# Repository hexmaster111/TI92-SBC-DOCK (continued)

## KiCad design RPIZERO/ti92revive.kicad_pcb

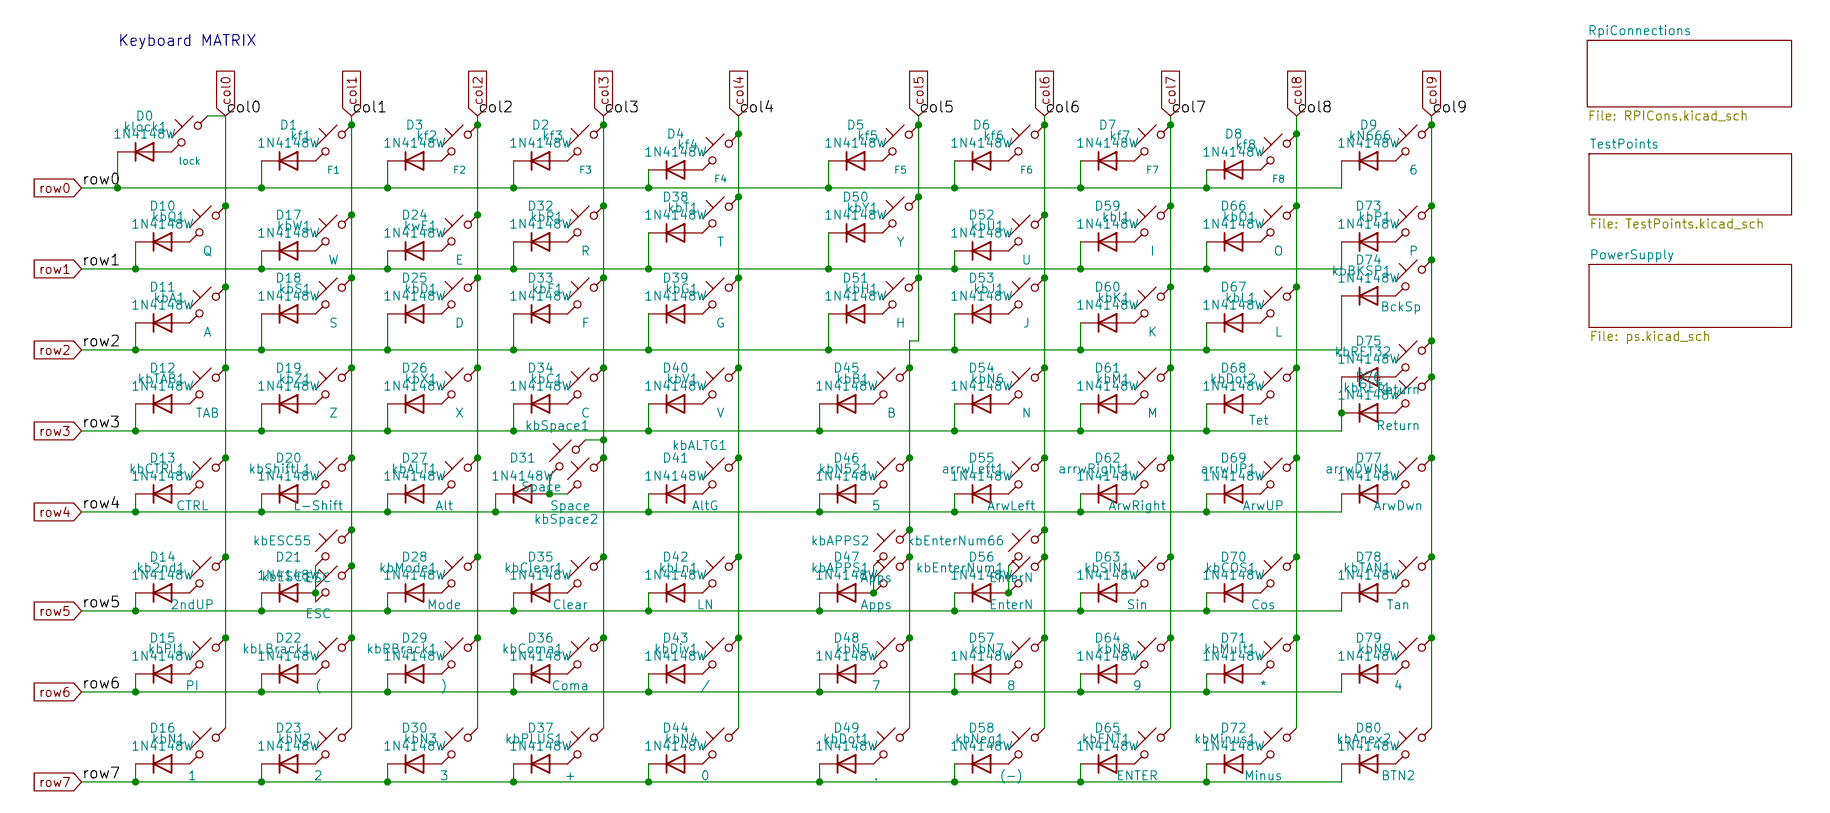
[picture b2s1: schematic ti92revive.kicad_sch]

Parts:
D0, D1, D2, D3, D4, D5, D6, D7, D8, D9, D10, D11, D12, D13, D14, D15, D16, D17, D18, D19, D20, D21, D22, D23, D24, D25, D26, D27, D28, D29, D30, D31, D32, D33, D34, D35, D36, D37, D38, D39, D40, D41, D42, D43, D44, D45, D46, D47, D48, D49, D50, D51, D52, D53, D54, D55, D56, D57, D58, D59, D60, D61, D62, D63, D64, D65, D66, D67, D68, D69, D70, D71, D72, D73, D74, D75, D76, D77, D78, D79, D80: 1N4148W; D_SOD-123
arrwDWN1: ArwDwn; SW_SPST_B3SL-1002P
arrwLeft1: ArwLeft; SW_SPST_B3SL-1002P
arrwRight1: ArwRight; SW_SPST_B3SL-1002P
arrwUP1: ArwUP; SW_SPST_B3SL-1002P
kN666: 6; Kbpad
kb2nd1: 2ndUP; SW_SPST_B3SL-1002P
kbA1: A; SW_SPST_B3SL-1002P
kbALT1: Alt; SW_SPST_B3SL-1002P
kbALTG1: AltG; SW_SPST_B3SL-1002P
kbAPPS1: Apps; SW_SPST_B3SL-1002P
kbAPPS2: Apps; Kbpad
kbAnex2: BTN2; Kbpad
kbB1: B; SW_SPST_B3SL-1002P
kbBKSP1: BckSp; SW_SPST_B3SL-1002P
kbC1: C; SW_SPST_B3SL-1002P
kbCOS1: Cos; SW_SPST_B3SL-1002P
kbCTRL1: CTRL; SW_SPST_B3SL-1002P
kbClear1: Clear; SW_SPST_B3SL-1002P
kbComa1: Coma; SW_SPST_B3SL-1002P
kbD1: D; SW_SPST_B3SL-1002P
kbDiv1: /; SW_SPST_B3SL-1002P
kbDot1: .; SW_SPST_B3SL-1002P
kbDot2: Tet; SW_SPST_B3SL-1002P
kbENT1: ENTER; SW_SPST_B3SL-1002P
kbESC1, kbESC55: ESC; SW_SPST_B3SL-1002P
kbEnterNum1, kbEnterNum66: EnterN; Kbpad
kbF1: F; SW_SPST_B3SL-1002P
kbG1: G; SW_SPST_B3SL-1002P
kbH1: H; SW_SPST_B3SL-1002P
kbI1: I; SW_SPST_B3SL-1002P
kbJ1: J; SW_SPST_B3SL-1002P
kbK1: K; SW_SPST_B3SL-1002P
kbL1: L; SW_SPST_B3SL-1002P
kbLBrack1: (; SW_SPST_B3SL-1002P
kbLn1: LN; SW_SPST_B3SL-1002P
kbM1: M; SW_SPST_B3SL-1002P
kbMinus1: Minus; Kbpad
kbMode1: Mode; SW_SPST_B3SL-1002P
kbMult1: *; SW_SPST_B3SL-1002P
kbN1: 1; SW_SPST_B3SL-1002P
kbN2: 2; SW_SPST_B3SL-1002P
kbN3: 3; SW_SPST_B3SL-1002P
kbN4: 0; SW_SPST_B3SL-1002P
kbN5: 7; SW_SPST_B3SL-1002P
kbN6: N; SW_SPST_B3SL-1002P
kbN7: 8; Kbpad
kbN8: 9; SW_SPST_B3SL-1002P
kbN9: 4; Kbpad
kbN521: 5; Kbpad
kbNeg1: (-); Kbpad
kbO1: O; SW_SPST_B3SL-1002P
kbP1: P; SW_SPST_B3SL-1002P
kbPI1: PI; SW_SPST_B3SL-1002P
kbPLUS1: +; SW_SPST_B3SL-1002P
kbQ1: Q; SW_SPST_B3SL-1002P
kbR1: R; SW_SPST_B3SL-1002P
kbRBrack1: ); SW_SPST_B3SL-1002P
kbRET1, kbRET32: Return; SW_SPST_B3SL-1002P
kbS1: S; SW_SPST_B3SL-1002P
kbSIN1: Sin; SW_SPST_B3SL-1002P
kbShiftL1: L-Shift; SW_SPST_B3SL-1002P
kbSpace1, kbSpace2: Space; SW_SPST_B3SL-1002P
kbT1: T; SW_SPST_B3SL-1002P
kbTAB1: TAB; SW_SPST_B3SL-1002P
kbTAN1: Tan; Kbpad
kbU1: U; SW_SPST_B3SL-1002P
kbV1: V; SW_SPST_B3SL-1002P
kbW1: W; SW_SPST_B3SL-1002P
kbX1: X; SW_SPST_B3SL-1002P
kbY1: Y; SW_SPST_B3SL-1002P
kbZ1: Z; SW_SPST_B3SL-1002P
kf1: F1; Kbpad
kf2: F2; Kbpad
kf3: F3; Kbpad
kf4: F4; SW_SPST_B3SL-1002P
kf5: F5; SW_SPST_B3SL-1002P
kf6: F6; SW_SPST_B3SL-1002P
kf7: F7; SW_SPST_B3SL-1002P
kf8: F8; SW_SPST_B3SL-1002P
klock1: lock; Kbpad
kwE1: E; SW_SPST_B3SL-1002P

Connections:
unnamed: D0.2 (A), klock1.2
unnamed: D1.2 (A), kf1.2
unnamed: D2.2 (A), kf3.2
unnamed: D3.2 (A), kf2.2
unnamed: D4.2 (A), kf4.2
unnamed: D5.2 (A), kf5.2
unnamed: D6.2 (A), kf6.2
unnamed: D7.2 (A), kf7.2
unnamed: D8.2 (A), kf8.2
unnamed: D9.2 (A), kN666.2
unnamed: D10.2 (A), kbQ1.2
unnamed: D11.2 (A), kbA1.2
unnamed: D12.2 (A), kbTAB1.2
unnamed: D13.2 (A), kbCTRL1.2
unnamed: D14.2 (A), kb2nd1.2
unnamed: D15.2 (A), kbPI1.2
unnamed: D16.2 (A), kbN1.2
unnamed: D17.2 (A), kbW1.2
unnamed: D18.2 (A), kbS1.2
unnamed: D19.2 (A), kbZ1.2
unnamed: D20.2 (A), kbShiftL1.2
unnamed: D21.2 (A), kbESC1.2, kbESC55.2
unnamed: D22.2 (A), kbLBrack1.2
unnamed: D23.2 (A), kbN2.2
unnamed: D24.2 (A), kwE1.2
unnamed: D25.2 (A), kbD1.2
unnamed: D26.2 (A), kbX1.2
unnamed: D27.2 (A), kbALT1.2
unnamed: D28.2 (A), kbMode1.2
unnamed: D29.2 (A), kbRBrack1.2
unnamed: D30.2 (A), kbN3.2
unnamed: D31.2 (A), kbSpace1.2, kbSpace2.2
unnamed: D32.2 (A), kbR1.2
unnamed: D33.2 (A), kbF1.2
unnamed: D34.2 (A), kbC1.2
unnamed: D35.2 (A), kbClear1.2
unnamed: D36.2 (A), kbComa1.2
unnamed: D37.2 (A), kbPLUS1.2
unnamed: D38.2 (A), kbT1.2
unnamed: D39.2 (A), kbG1.2
unnamed: D40.2 (A), kbV1.2
unnamed: D41.2 (A), kbALTG1.2
unnamed: D42.2 (A), kbLn1.2
unnamed: D43.2 (A), kbDiv1.2
unnamed: D44.2 (A), kbN4.2
unnamed: D45.2 (A), kbB1.2
unnamed: D46.2 (A), kbN521.2
unnamed: D47.2 (A), kbAPPS1.2, kbAPPS2.2
unnamed: D48.2 (A), kbN5.2
unnamed: D49.2 (A), kbDot1.2
unnamed: D50.2 (A), kbY1.2
unnamed: D51.2 (A), kbH1.2
unnamed: D52.2 (A), kbU1.2
unnamed: D53.2 (A), kbJ1.2
unnamed: D54.2 (A), kbN6.2
unnamed: D55.2 (A), arrwLeft1.2
unnamed: D56.2 (A), kbEnterNum1.2, kbEnterNum66.2
unnamed: D57.2 (A), kbN7.2
unnamed: D58.2 (A), kbNeg1.2
unnamed: D59.2 (A), kbI1.2
unnamed: D60.2 (A), kbK1.2
unnamed: D61.2 (A), kbM1.2
unnamed: D62.2 (A), arrwRight1.2
unnamed: D63.2 (A), kbSIN1.2
unnamed: D64.2 (A), kbN8.2
unnamed: D65.2 (A), kbENT1.2
unnamed: D66.2 (A), kbO1.2
unnamed: D67.2 (A), kbL1.2
unnamed: D68.2 (A), kbDot2.2
unnamed: D69.2 (A), arrwUP1.2
unnamed: D70.2 (A), kbCOS1.2
unnamed: D71.2 (A), kbMult1.2
unnamed: D72.2 (A), kbMinus1.2
unnamed: D73.2 (A), kbP1.2
unnamed: D74.2 (A), kbBKSP1.2
unnamed: D75.2 (A), kbRET32.2
unnamed: D76.2 (A), kbRET1.2
unnamed: D77.2 (A), arrwDWN1.2
unnamed: D78.2 (A), kbTAN1.2
unnamed: D79.2 (A), kbN9.2
unnamed: D80.2 (A), kbAnex2.2
col0: kb2nd1.1, kbA1.1, kbCTRL1.1, kbN1.1, kbPI1.1, kbQ1.1, kbTAB1.1, klock1.1; also elsewhere on the board
col1: kbESC1.1, kbESC55.1, kbLBrack1.1, kbN2.1, kbS1.1, kbShiftL1.1, kbW1.1, kbZ1.1, kf1.1; also elsewhere on the board
col2: kbALT1.1, kbD1.1, kbMode1.1, kbN3.1, kbRBrack1.1, kbX1.1, kf2.1, kwE1.1
col3: kbC1.1, kbClear1.1, kbComa1.1, kbF1.1, kbPLUS1.1, kbR1.1, kbSpace1.1, kbSpace2.1, kf3.1; also elsewhere on the board
col4: kbALTG1.1, kbDiv1.1, kbG1.1, kbLn1.1, kbN4.1, kbT1.1, kbV1.1, kf4.1; also elsewhere on the board
col5: kbAPPS1.1, kbAPPS2.1, kbB1.1, kbDot1.1, kbH1.1, kbN5.1, kbN521.1, kbY1.1, kf5.1; also elsewhere on the board
col6: arrwLeft1.1, kbEnterNum1.1, kbEnterNum66.1, kbJ1.1, kbN6.1, kbN7.1, kbNeg1.1, kbU1.1, kf6.1; also elsewhere on the board
col7: arrwRight1.1, kbENT1.1, kbI1.1, kbK1.1, kbM1.1, kbN8.1, kbSIN1.1, kf7.1; also elsewhere on the board
col8: arrwUP1.1, kbCOS1.1, kbDot2.1, kbL1.1, kbMinus1.1, kbMult1.1, kbO1.1, kf8.1; also elsewhere on the board
col9: arrwDWN1.1, kN666.1, kbAnex2.1, kbBKSP1.1, kbN9.1, kbP1.1, kbRET1.1, kbRET32.1, kbTAN1.1
row0: D0.1 (K), D1.1 (K), D2.1 (K), D3.1 (K), D4.1 (K), D5.1 (K), D6.1 (K), D7.1 (K), D8.1 (K), D9.1 (K); also elsewhere on the board
row1: D10.1 (K), D17.1 (K), D24.1 (K), D32.1 (K), D38.1 (K), D50.1 (K), D52.1 (K), D59.1 (K), D66.1 (K), D73.1 (K); also elsewhere on the board
row2: D11.1 (K), D18.1 (K), D25.1 (K), D33.1 (K), D39.1 (K), D51.1 (K), D53.1 (K), D60.1 (K), D67.1 (K), D74.1 (K); also elsewhere on the board
row3: D12.1 (K), D19.1 (K), D26.1 (K), D34.1 (K), D40.1 (K), D45.1 (K), D54.1 (K), D61.1 (K), D68.1 (K), D75.1 (K), D76.1 (K); also elsewhere on the board
row4: D13.1 (K), D20.1 (K), D27.1 (K), D31.1 (K), D41.1 (K), D46.1 (K), D55.1 (K), D62.1 (K), D69.1 (K), D77.1 (K); also elsewhere on the board
row5: D14.1 (K), D21.1 (K), D28.1 (K), D35.1 (K), D42.1 (K), D47.1 (K), D56.1 (K), D63.1 (K), D70.1 (K), D78.1 (K); also elsewhere on the board
row6: D15.1 (K), D22.1 (K), D29.1 (K), D36.1 (K), D43.1 (K), D48.1 (K), D57.1 (K), D64.1 (K), D71.1 (K), D79.1 (K); also elsewhere on the board
row7: D16.1 (K), D23.1 (K), D30.1 (K), D37.1 (K), D44.1 (K), D49.1 (K), D58.1 (K), D65.1 (K), D72.1 (K), D80.1 (K); also elsewhere on the board

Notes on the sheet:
Keyboard MATRIX

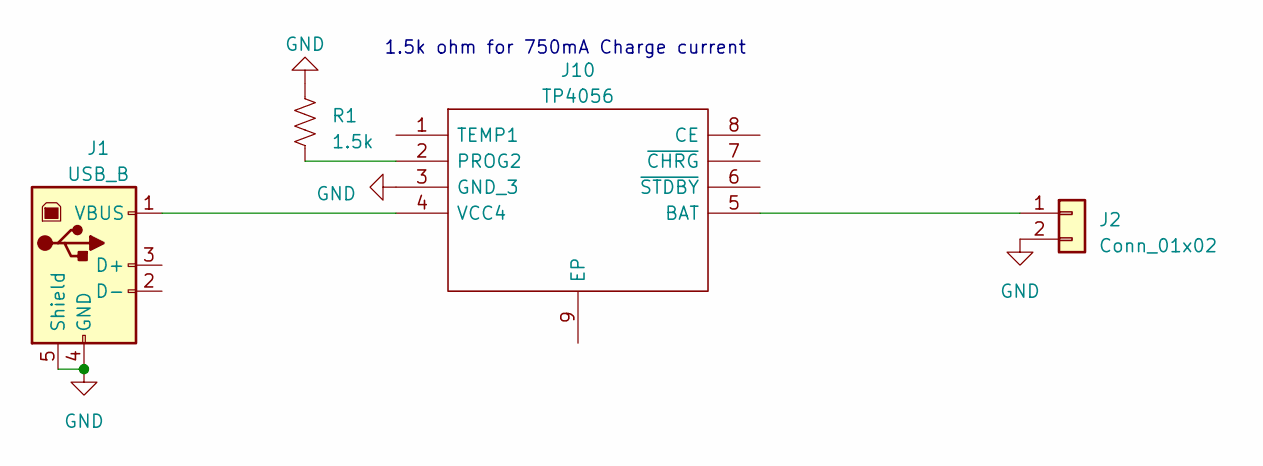
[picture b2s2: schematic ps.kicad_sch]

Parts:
J1: USB_B; USB_Micro-B_Amphenol_10103594-0001LF_Horizontal
J2: Conn_01x02; JST_PH_B2B-PH-K_1x02_P2.00mm_Vertical
J10: TP4056; SOIC127P600X175-9N; Manufacturer_Part_Number TP4056
R1: 1.5k; R_2010_5025Metric

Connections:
GND: J1.4 (GND), J1.5 (Shield), J2.2, J10.3 (GND_3), R1.2; also elsewhere on the board
unnamed: J1.1 (VBUS), J10.4 (VCC4)
unnamed: J10.2 (PROG2), R1.1
unnamed: J2.1, J10.5 (BAT)

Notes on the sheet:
1.5k ohm for 750mA Charge current

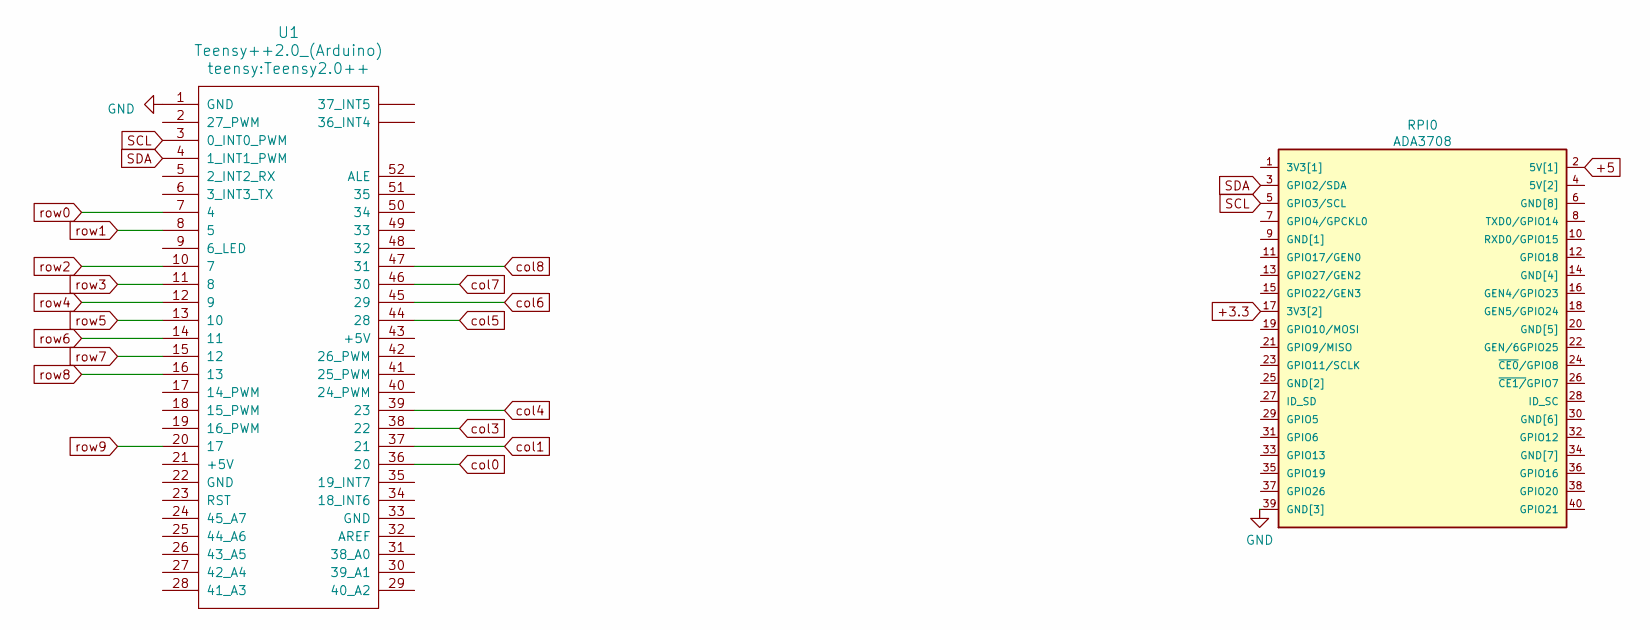
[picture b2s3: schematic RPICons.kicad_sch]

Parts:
RPI0: ADA3708; ADA3708_RPI-ZERO
U1: Teensy++2.0_(Arduino); Teensy2.0++

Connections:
+3.3: RPI0.17 (3V3[2]); also elsewhere on the board
+5: RPI0.2 (5V[1]); also elsewhere on the board
GND: RPI0.39 (GND[3]), U1.1 (GND); also elsewhere on the board
SCL: RPI0.5 (GPIO3/SCL), U1.3 (0_INT0_PWM); also elsewhere on the board
SDA: RPI0.3 (GPIO2/SDA), U1.4 (1_INT1_PWM); also elsewhere on the board
col0: U1.36 (20); also elsewhere on the board
col1: U1.37 (21); also elsewhere on the board
col3: U1.38 (22); also elsewhere on the board
col4: U1.39 (23); also elsewhere on the board
col5: U1.44 (28); also elsewhere on the board
col6: U1.45 (29); also elsewhere on the board
col7: U1.46 (30); also elsewhere on the board
col8: U1.47 (31); also elsewhere on the board
row0: U1.7 (4); also elsewhere on the board
row1: U1.8 (5); also elsewhere on the board
row2: U1.10 (7); also elsewhere on the board
row3: U1.11 (8); also elsewhere on the board
row4: U1.12 (9); also elsewhere on the board
row5: U1.13 (10); also elsewhere on the board
row6: U1.14 (11); also elsewhere on the board
row7: U1.15 (12); also elsewhere on the board
row8: U1.16 (13)
row9: U1.20 (17)

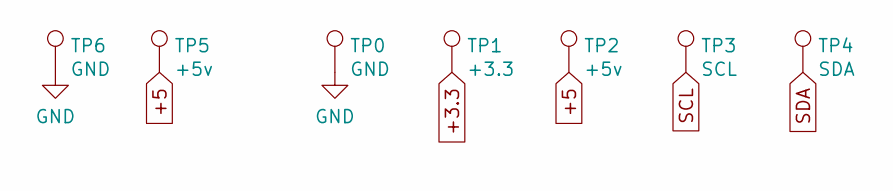
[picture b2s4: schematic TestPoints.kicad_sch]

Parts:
TP0, TP6: GND; TestPoint_Pad_D1.5mm
TP1: +3.3; TestPoint_Pad_D1.5mm
TP2, TP5: +5v; TestPoint_Pad_D1.5mm
TP3: SCL; TestPoint_Pad_D1.5mm
TP4: SDA; TestPoint_Pad_D1.5mm

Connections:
+3.3: TP1.1; also elsewhere on the board
+5: TP2.1, TP5.1; also elsewhere on the board
GND: TP0.1, TP6.1; also elsewhere on the board
SCL: TP3.1; also elsewhere on the board
SDA: TP4.1; also elsewhere on the board

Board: 2 copper layers, 179 parts (92 on the bottom side), 107 nets, no tracks yet.

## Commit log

2021-04-13 new repo
2021-04-13 Adding Stuff to the project
    Yee, doing it
2021-04-14 Clean up and resetting to do the compute modual version
2021-04-14 Push before big change
    Chaing the charge controll Stuffs
2021-04-14 Working on adding new charge controller
2021-04-15 BatteryCharging COMPLEATE
2021-04-15 Laid out 5v ic and battery charger
2021-04-15 Added Power Button Control Circuit
2021-04-15 cleanup
2021-04-16 Added Power Control Relay
    also cleaned up some junk and jank
2021-04-16 Wrote program discription
2021-04-16 Removed Keyboard Matrix Diodes and Added PowerLED and ActivityLED
2021-04-16 Added Keyboard Matrix Map
2021-04-17 Added high current 3.3v supply
2021-04-19 Added USB Hub Contoler and usb port internal and external
2021-04-19 Added Keyboard matrix controller and indicator leds
2021-04-19 Cleaned Up the Matrix contolller
2021-04-19 added battery connecoectors and emmcbootdisable jumpper
2021-04-19 Removing The backups folder from the git repo
2021-04-20 Finally Added the display!!!!
2021-04-21 Started the "fun" of routing
2021-04-21 i hate routing
2021-04-21 Heck Routing
2021-04-21 Wow, This is kinda fun
2021-04-21 More wires hehehehe
    wow so good
2021-04-21 Keyboard close to done
2021-04-21 Keyboard Done <3
    adding a layer for signals that need to be *Clean*
2021-04-21 boys we got 2 more layers to play with now >.<
    (oh god this is so much stuff hehehehehehe.... ima go mad with power)
2021-04-21 routing fun!!
2021-04-21 100 things left to rout
2021-04-21 75 left to go
2021-04-21 Everything is routed
    Just waiting on display to finsh routing that, then its time to get some pcbs on the way and cross my fingers that i dont cook a cm4 >.<
2021-04-21 Adding image for readme
2021-05-28 Bigone here we go
    Whats gonna happon is im gonna get a 4 inch hdmi display and desolder the hdmi connector and add it to a ribbion cable and then add a connector to the pcb for hdmi to interface with that
2021-05-31 adding hdmi connector
2021-05-31 PrepedHDMIConnections
2021-05-31 Removed Jumpers and just doing hdmi the right way the first time, this wont bite me in the butt
2021-06-01 added sdcard
2021-06-02 display done
2021-06-02 Compleated REV001
2021-06-02 no more uvias
